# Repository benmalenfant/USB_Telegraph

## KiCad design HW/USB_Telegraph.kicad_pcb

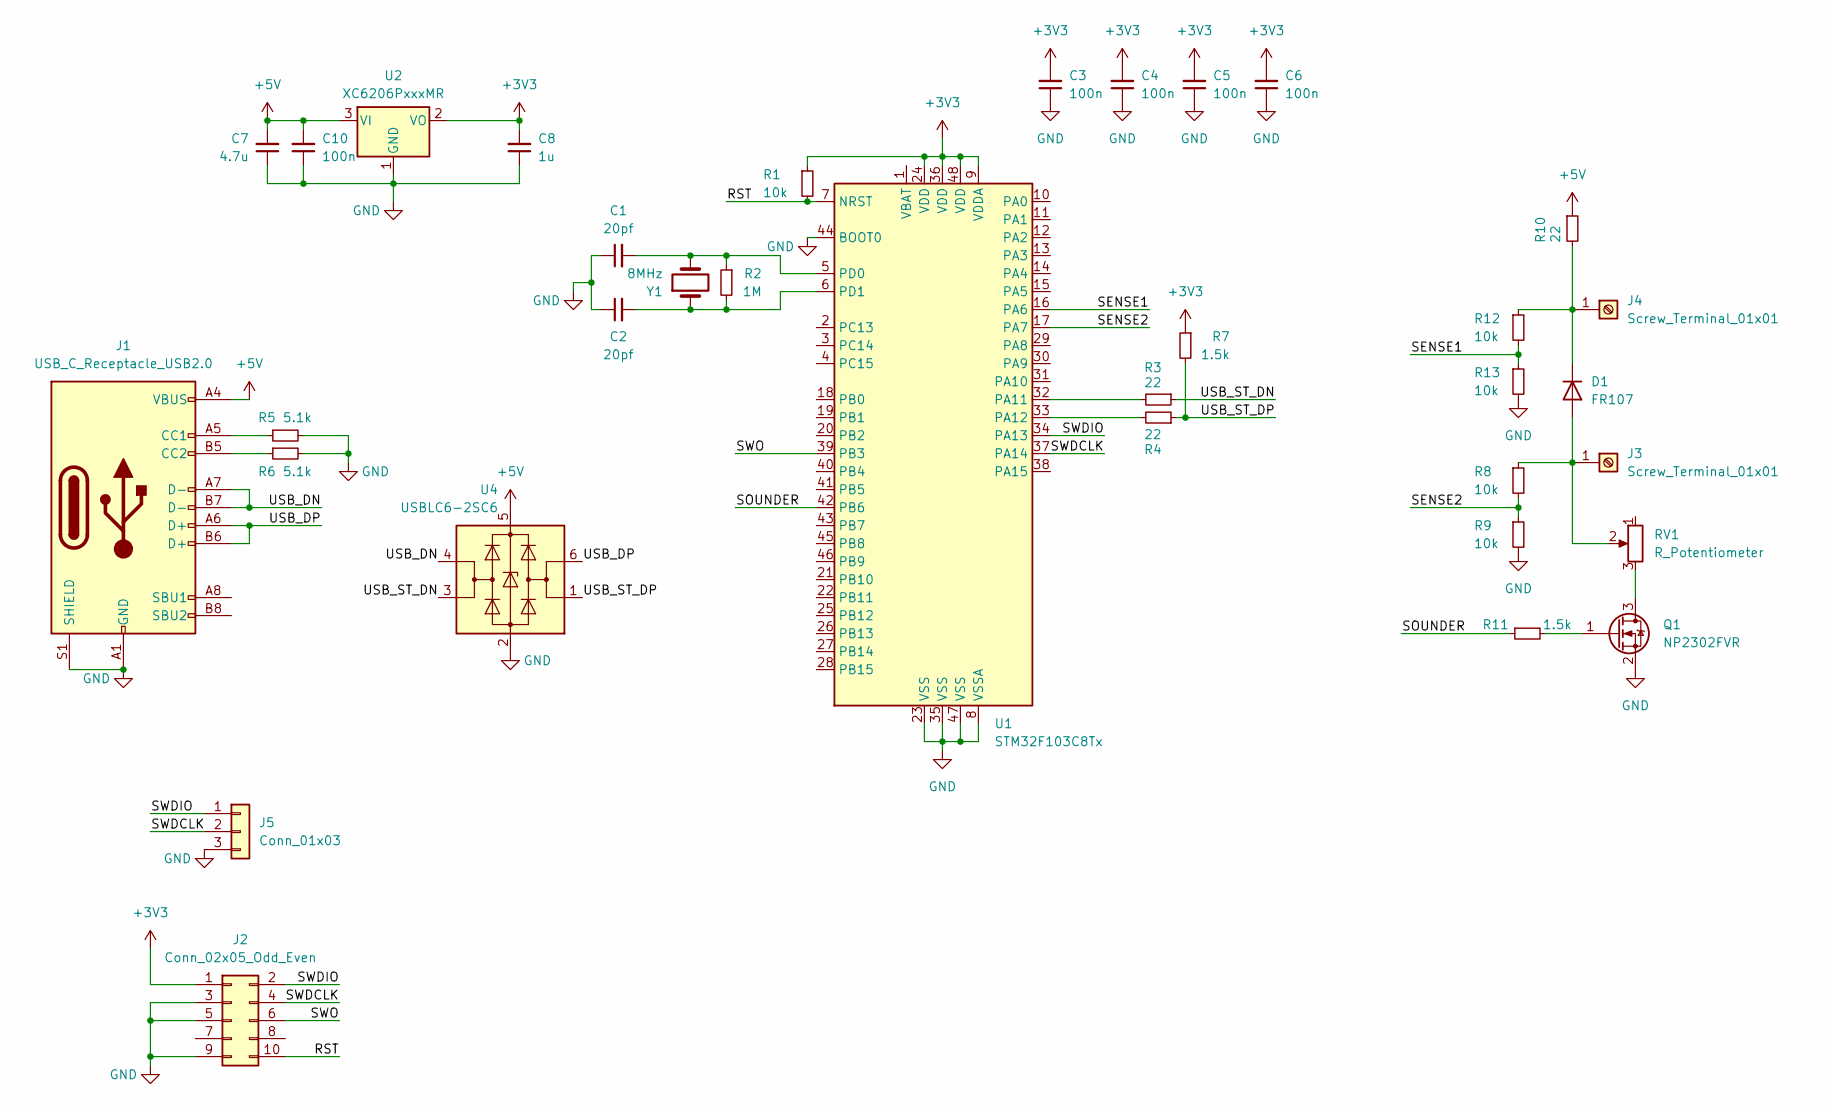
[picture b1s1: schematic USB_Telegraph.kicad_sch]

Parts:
C1, C2: 20pf; C_0402_1005Metric
C3, C4, C5, C6, C10: 100n; C_0402_1005Metric
C7: 4.7u; C_0402_1005Metric
C8: 1u; C_0402_1005Metric
D1: FR107; D_SOD-123F
J1: USB_C_Receptacle_USB2.0; USB_C_Receptacle_G-Switch_GT-USB-7010ASV
J2: Conn_02x05_Odd_Even; PinHeader_2x05_P1.27mm_Vertical_SMD
J3, J4: Screw_Terminal_01x01; M4 plated
J5: Conn_01x03; PinSocket_1x03_P2.54mm_Horizontal
Q1: NP2302FVR; SOT-23
R1, R8, R9, R12, R13: 10k; R_0402_1005Metric
R2: 1M; R_0402_1005Metric
R3, R4: 22; R_0402_1005Metric
R5, R6: 5.1k; R_0402_1005Metric
R7, R11: 1.5k; R_0402_1005Metric
R10: 22; R_2010_5025Metric
RV1: R_Potentiometer; Potentiometer_Bourns_3314J_Vertical
U1: STM32F103C8Tx; LQFP-48_7x7mm_P0.5mm
U2: XC6206PxxxMR; SOT-23
U4: USBLC6-2SC6; SOT-23-6
Y1: 8MHz; Crystal_SMD_3225-4Pin_3.2x2.5mm

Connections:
+3V3: C3.2, C4.2, C5.2, C6.2, C8.2, J2.1, R1.1, R7.1, U1.9 (VDDA), U1.24 (VDD), U1.36 (VDD), U1.48 (VDD), U2.2 (VO)
+5V: C7.2, C10.2, J1.A4 (VBUS), J1.A9 (VBUS), J1.B4 (VBUS), J1.B9 (VBUS), R10.1, U2.3 (VI), U4.5 (VBUS)
/RST: J2.10, R1.2, U1.7 (NRST)
/SENSE1: R12.2, R13.1, U1.16 (PA6)
/SENSE2: R8.2, R9.1, U1.17 (PA7)
/SOUNDER: R11.1, U1.42 (PB6)
/SWDCLK: J2.4, J5.2, U1.37 (PA14)
/SWDIO: J2.2, J5.1, U1.34 (PA13)
/SWO: J2.6, U1.39 (PB3)
/USB_DN: J1.A7 (D-), J1.B7 (D-), U4.4 (I/O2)
/USB_DP: J1.A6 (D+), J1.B6 (D+), U4.6 (I/O1)
/USB_ST_DN: R3.1, U4.3 (I/O2)
/USB_ST_DP: R4.1, R7.2, U4.1 (I/O1)
GND: C1.1, C2.1, C3.1, C4.1, C5.1, C6.1, C7.1, C8.1, C10.1, J1.A1 (GND), J1.A12 (GND), J1.B1 (GND), J1.B12 (GND), J1.S1 (SHIELD), J2.3, J2.5, J2.9, J5.3, Q1.2 (S), R5.2, R6.2, R9.2, R13.2, U1.8 (VSSA), U1.23 (VSS), U1.35 (VSS), U1.44 (BOOT0), U1.47 (VSS), U2.1 (GND), U4.2 (GND)
unnamed: D1.2 (A), J3.1, R8.1, RV1.2
unnamed: D1.1 (K), J4.1, R10.2, R12.1
unnamed: J1.A5 (CC1), R5.1
unnamed: J1.B5 (CC2), R6.1
unnamed: Q1.3 (D), RV1.3
unnamed: Q1.1 (G), R11.2
unnamed: R3.2, U1.32 (PA11)
unnamed: R4.2, U1.33 (PA12)
unnamed: C1.2, R2.1, U1.5 (PD0), Y1.2
unnamed: C2.2, R2.2, U1.6 (PD1), Y1.1

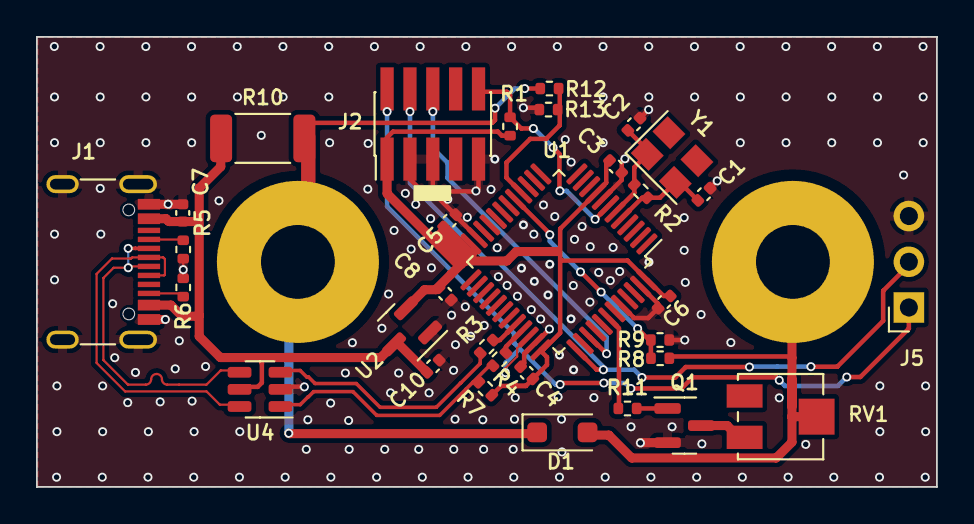
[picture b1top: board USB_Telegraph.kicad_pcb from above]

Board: 2 copper layers, 50.0 x 25.0 mm, 34 parts (0 on the bottom side), 24 nets.

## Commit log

2024-02-07 Initial placement + keyboard firmware
2024-02-07 Initial routing
2024-02-07 Routing done, part assignement done
2024-02-08 add fab outputs
2024-02-08 minor pcb changes
2024-02-13 changed via size
2024-05-05 add firmware for online operation - need rename
2024-05-05 SW First commit
2024-05-05 Untrack fab_outputs
2024-05-05 working client
2024-05-05 update firmware to work in response mode
2024-05-05 update client and server-first semi stable
2024-05-05 V1 - first working version
2024-05-06 rename fw_serial
